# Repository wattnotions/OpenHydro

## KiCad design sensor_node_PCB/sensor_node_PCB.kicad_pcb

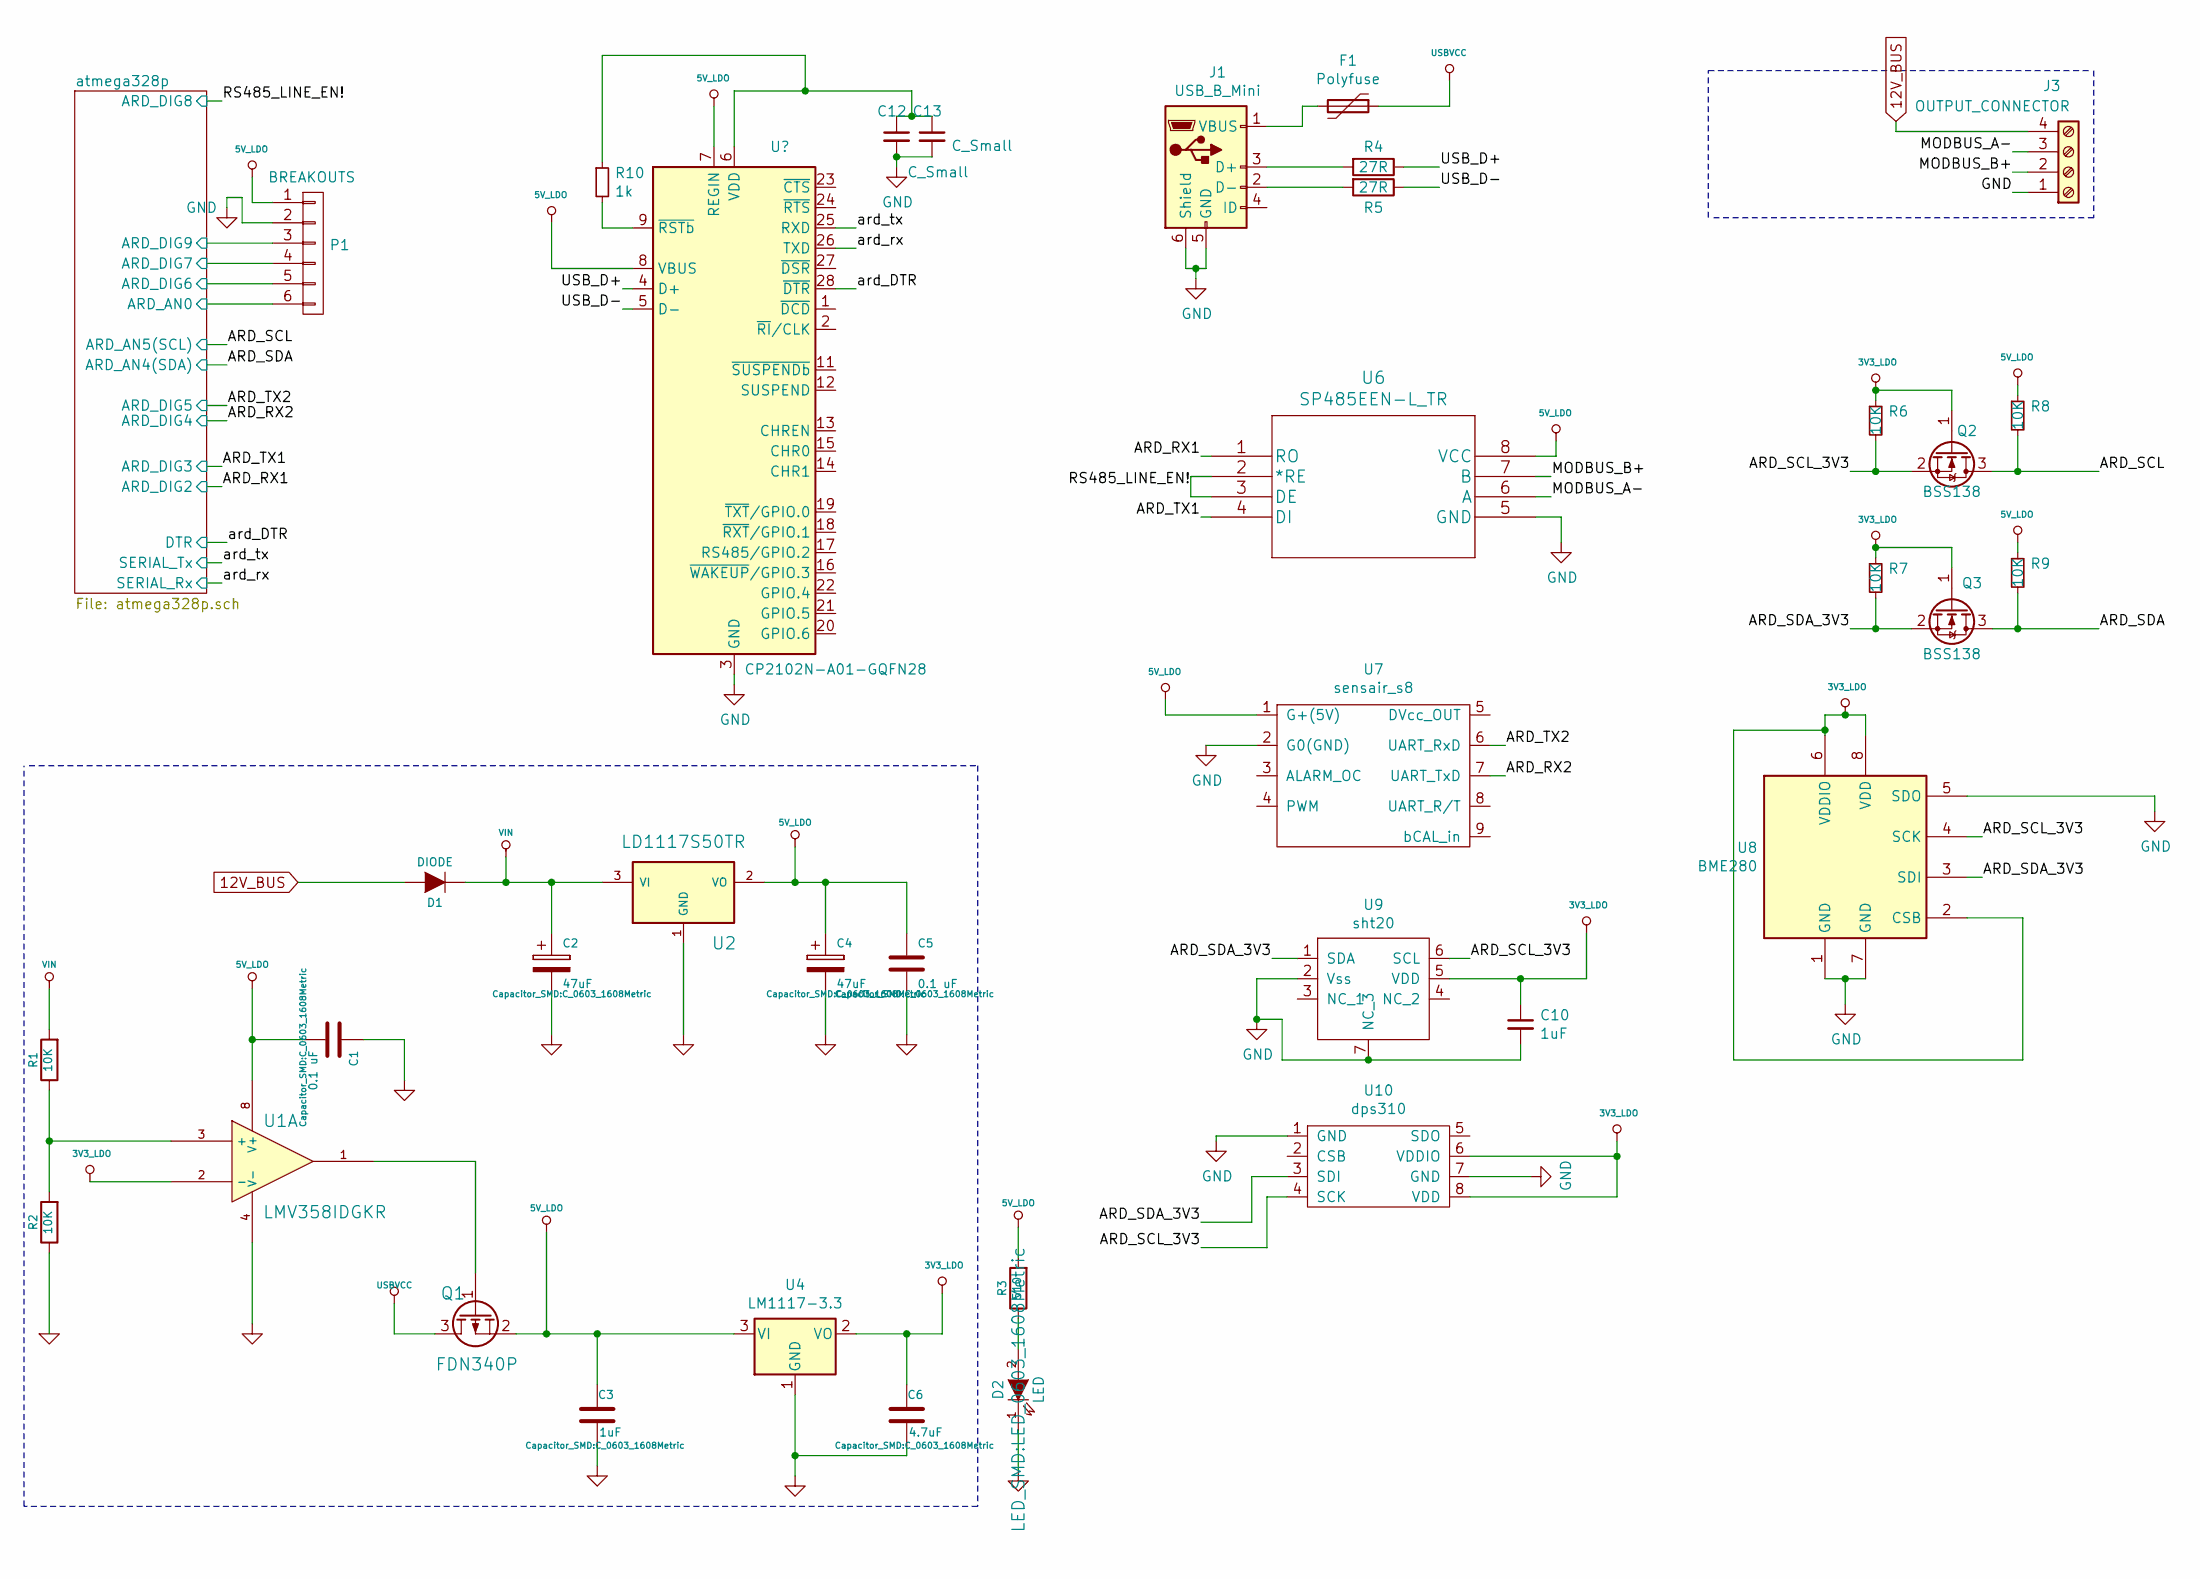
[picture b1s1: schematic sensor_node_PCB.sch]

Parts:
C1, C5: 0.1 uF; C_0603_1608Metric
C2, C4: 47uF; C_0603_1608Metric
C3, C10: 1uF; C_0603_1608Metric
C6: 4.7uF; C_0603_1608Metric
C12, C13: C_Small; C_0603_1608Metric
D1: DIODE; D_SOD-123
D2: LED; LED_0603_1608Metric
F1: Polyfuse; Fuse_1206_3216Metric
J1: USB_B_Mini; USB_Mini-B_Tensility_54-00023_Vertical
J3: OUTPUT_CONNECTOR; PhoenixContact_MSTB_2,5_4-GF-5,08_1x04_P5.08mm_Horizontal_T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
P1: BREAKOUTS; TerminalBlock_bornier-6_P5.08mm
Q1: FDN340P; SuperSOT-3
Q2, Q3: BSS138; SOT-23
R1, R2, R6, R7, R8, R9: 10K; R_0603_1608Metric
R3: 510; R_0603_1608Metric
R4, R5: 27R; R_0603_1608Metric
R10: 1k; R_0603_1608Metric
U1: LMV358IDGKR; SOIC-8_3.9x4.9mm_P1.27mm
U2: LD1117S50TR; SOT-223-3_TabPin2
U4: LM1117-3.3; SOT-223-3_TabPin2
U6: SP485EEN-L_TR; SOIC-8_3.9x4.9mm_P1.27mm
U7: sensair_s8; senseair_s8_v3
U8: BME280; Bosch_LGA-8_2.5x2.5mm_P0.65mm_ClockwisePinNumbering
U9: sht20; DFN-6-1EP_3x3mm_P1mm_EP1.5x2.4mm
U10: dps310; Bosch_LGA-8_2x2.5mm_P0.65mm_ClockwisePinNumbering

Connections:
3V3_LDO: C6.1, C10.1, Q2.1 (G), Q3.1 (G), R6.1, R7.1, U1.2 (-), U4.2 (VO), U8.2 (CSB), U8.6 (VDDIO), U8.8 (VDD), U9.5 (VDD), U10.6 (VDDIO), U10.8 (VDD)
5V_LDO: C1.2, C3.1, C4.1, C5.1, P1.1, Q1.2 (S), R3.2, R8.1, R9.1, U1.8 (V+), U2.2 (VO), U4.3 (VI), U6.8 (VCC), U7.1 (G+(5V)); also elsewhere on the board
12V_BUS: D1.2 (A), J3.4
/ARD_RX1: U6.1 (RO); also elsewhere on the board
/ARD_RX2: U7.7 (UART_TxD); also elsewhere on the board
/ARD_SCL: Q2.3 (D), R8.2; also elsewhere on the board
/ARD_SCL_3V3: Q2.2 (S), R6.2, U8.4 (SCK), U9.6 (SCL), U10.4 (SCK)
/ARD_SDA: Q3.3 (D), R9.2; also elsewhere on the board
/ARD_SDA_3V3: Q3.2 (S), R7.2, U8.3 (SDI), U9.1 (SDA), U10.3 (SDI)
/ARD_TX1: U6.4 (DI); also elsewhere on the board
/ARD_TX2: U7.6 (UART_RxD); also elsewhere on the board
/MODBUS_A-: J3.3, U6.6 (A)
/MODBUS_B+: J3.2, U6.7 (B)
/RS485_LINE_EN!: U6.2 (*RE), U6.3 (DE); also elsewhere on the board
/USB_D+: R4.1; also elsewhere on the board
/USB_D-: R5.1; also elsewhere on the board
/atmega328p/ARD_AN0: P1.6; also elsewhere on the board
/atmega328p/ARD_DIG6: P1.5; also elsewhere on the board
/atmega328p/ARD_DIG7: P1.4; also elsewhere on the board
/atmega328p/ARD_DIG9: P1.3; also elsewhere on the board
GND: C1.1, C2.2, C3.2, C4.2, C5.2, C6.2, C10.2, C12.2, C13.2, D2.1 (K), J1.5 (GND), J1.6 (Shield), J3.1, P1.2, R2.1, U1.4 (V-), U2.1 (GND), U4.1 (GND), U6.5 (GND), U7.2 (G0(GND)), U8.1 (GND), U8.5 (SDO), U8.7 (GND), U9.2 (Vss), U9.7 (NC_3), U10.1 (GND), U10.7 (GND); also elsewhere on the board
unnamed 32: C12.1, C13.1, R10.1; also elsewhere on the board
unnamed: D2.2 (A), R3.1
unnamed: F1.2, J1.1 (VBUS)
unnamed: J1.2 (D-), R5.2
unnamed: J1.3 (D+), R4.2
unnamed: Q1.1 (G), U1.1
unnamed: R1.1, R2.2, U1.3 (+)
unnamed 41: R10.2; also elsewhere on the board
USBVCC: F1.1, Q1.3 (D)
Vin: C2.1, D1.1 (K), R1.2, U2.3 (VI)

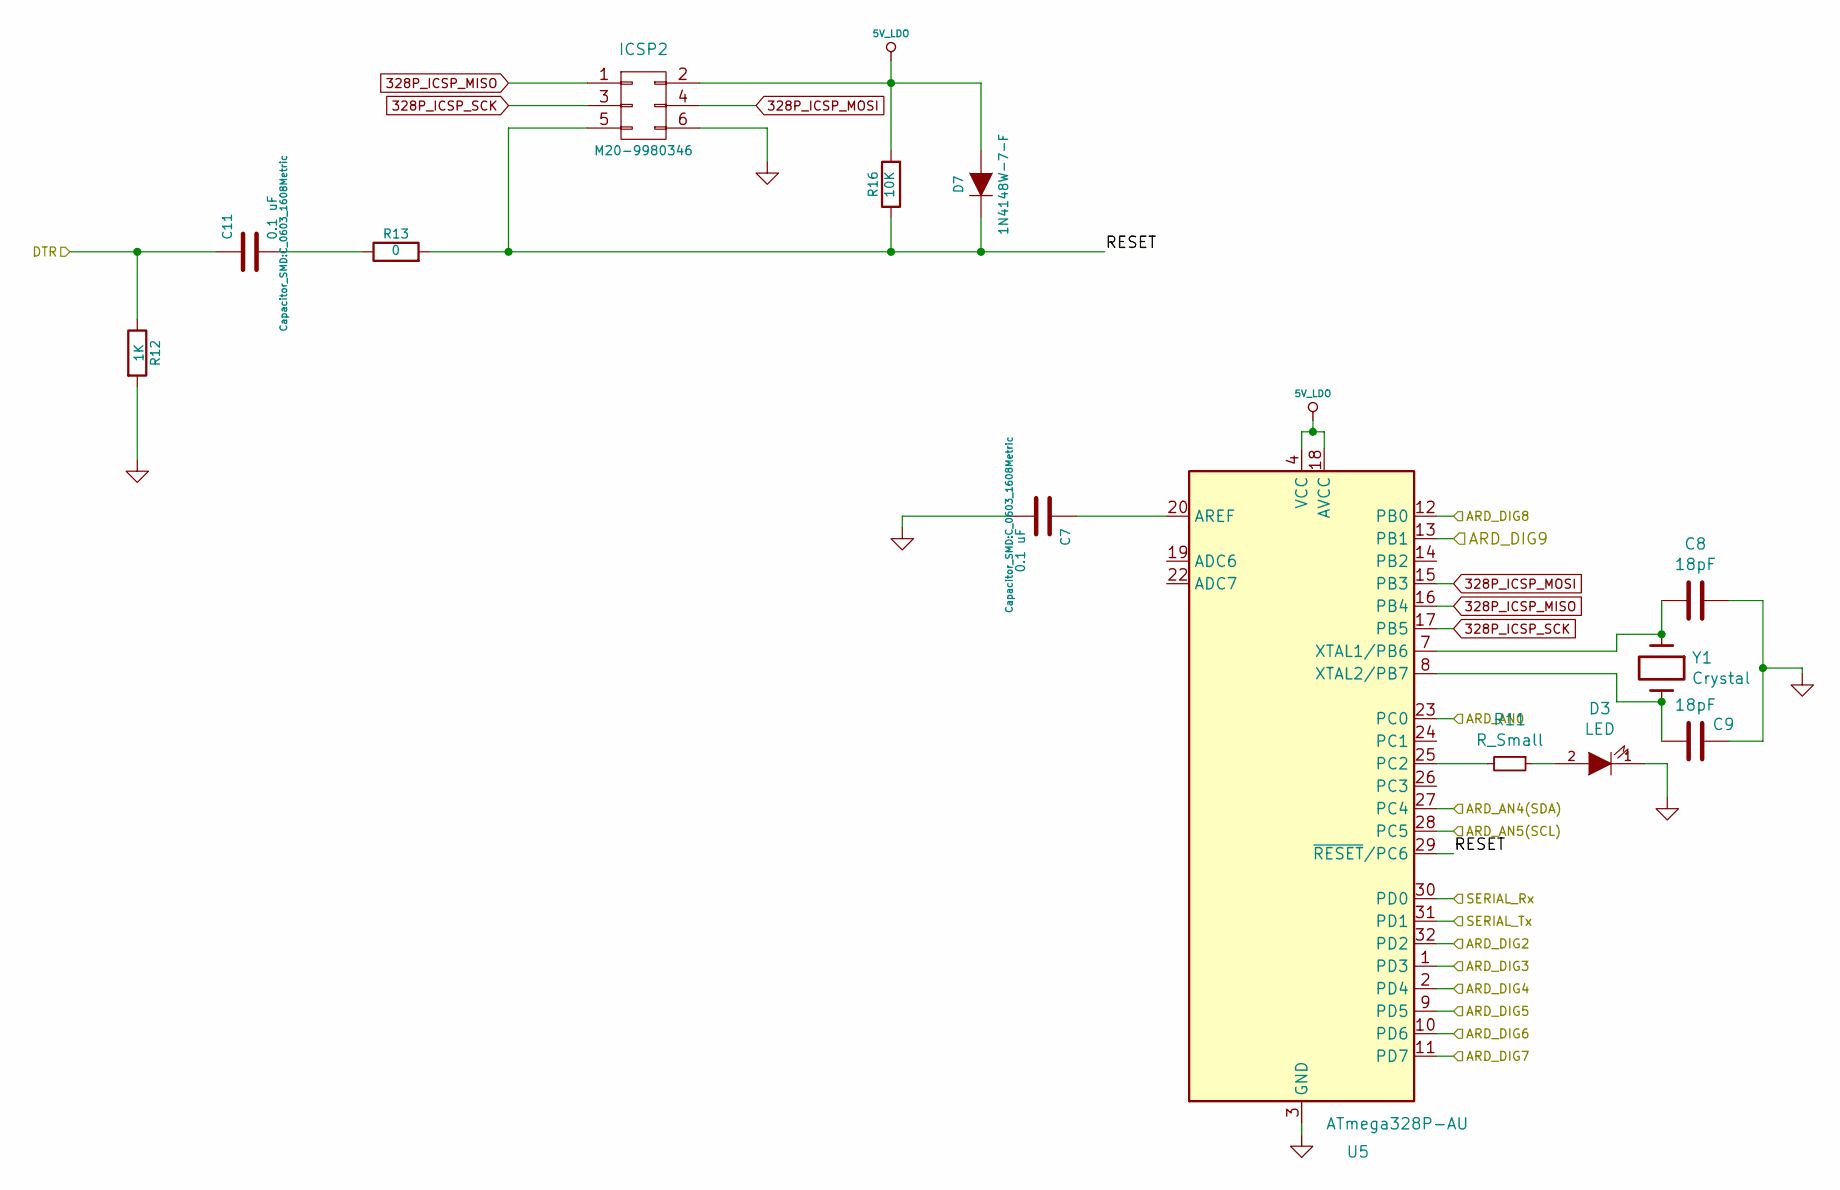
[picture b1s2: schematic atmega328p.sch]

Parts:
C7, C11: 0.1 uF; C_0603_1608Metric
C8, C9: 18pF; C_0603_1608Metric
D3: LED; LED_0603_1608Metric
D7: 1N4148W-7-F; D_SOD-123
ICSP2: M20-9980346; PinHeader_2x03_P2.54mm_Vertical_SMD
R11: R_Small; LED_0603_1608Metric
R12: 1K; R_0603_1608Metric
R13: 0; R_0603_1608Metric
R16: 10K; R_0603_1608Metric
U5: ATmega328P-AU; TQFP-32_7x7mm_P0.8mm
Y1: Crystal; Crystal_SMD_5032-2Pin_5.0x3.2mm

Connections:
5V_LDO: D7.2 (A), ICSP2.2, R16.2, U5.4 (VCC), U5.6 (VCC), U5.18 (AVCC); also elsewhere on the board
328P_ICSP_MISO: ICSP2.1, U5.16 (PB4)
328P_ICSP_MOSI: ICSP2.4, U5.15 (PB3)
328P_ICSP_SCK: ICSP2.3, U5.17 (PB5)
/ARD_RX1: U5.32 (PD2); also elsewhere on the board
/ARD_RX2: U5.2 (PD4); also elsewhere on the board
/ARD_SCL: U5.28 (PC5); also elsewhere on the board
/ARD_SDA: U5.27 (PC4); also elsewhere on the board
/ARD_TX1: U5.1 (PD3); also elsewhere on the board
/ARD_TX2: U5.9 (PD5); also elsewhere on the board
/RS485_LINE_EN!: U5.12 (PB0); also elsewhere on the board
/ard_DTR: C11.1, R12.1; also elsewhere on the board
/ard_rx: U5.30 (PD0); also elsewhere on the board
/ard_tx: U5.31 (PD1); also elsewhere on the board
/atmega328p/ARD_AN0: U5.23 (PC0); also elsewhere on the board
/atmega328p/ARD_DIG6: U5.10 (PD6); also elsewhere on the board
/atmega328p/ARD_DIG7: U5.11 (PD7); also elsewhere on the board
/atmega328p/ARD_DIG9: U5.13 (PB1); also elsewhere on the board
/atmega328p/RESET: D7.1 (K), ICSP2.5, R13.2, R16.1, U5.29 (~RESET~/PC6)
GND: C7.2, C8.1, C9.1, D3.1 (K), ICSP2.6, R12.2, U5.3 (GND), U5.5 (GND), U5.21 (GND); also elsewhere on the board
unnamed: C7.1, U5.20 (AREF)
unnamed: C8.2, U5.7 (XTAL1/PB6), Y1.1
unnamed: C9.2, U5.8 (XTAL2/PB7), Y1.2
unnamed: C11.2, R13.1
unnamed: D3.2 (A), R11.1
unnamed: R11.2, U5.25 (PC2)

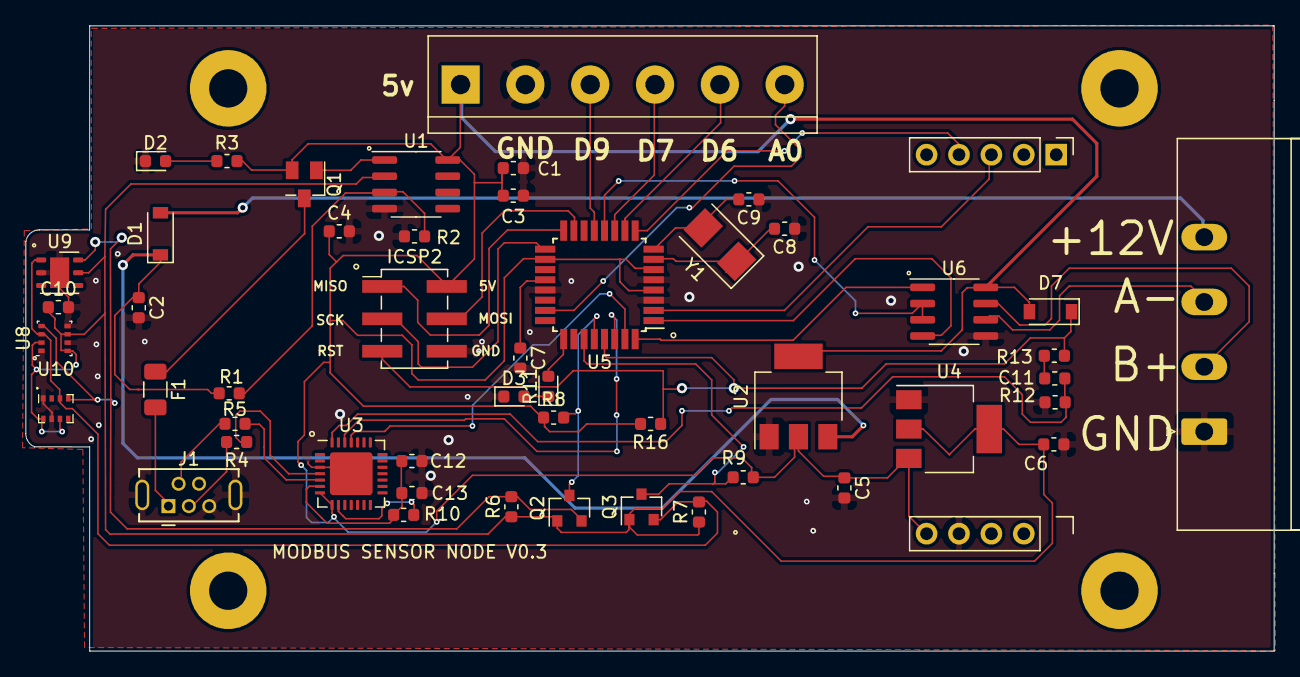
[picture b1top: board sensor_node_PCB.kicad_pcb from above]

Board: 2 copper layers, 97.8 x 49.0 mm, 50 parts (0 on the bottom side), 44 nets.

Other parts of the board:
U3: CP2102N-A01-GQFN28; QFN-28-1EP_5x5mm_P0.5mm_EP3.35x3.35mm

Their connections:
5V_LDO: U3.7, U3.8; also elsewhere on the board
/USB_D+: U3.4; also elsewhere on the board
/USB_D-: U3.5; also elsewhere on the board
/ard_DTR: U3.28; also elsewhere on the board
/ard_rx: U3.26; also elsewhere on the board
/ard_tx: U3.25; also elsewhere on the board
GND: U3.3, U3.29; also elsewhere on the board
unnamed 32: U3.6; also elsewhere on the board
unnamed 41: U3.9; also elsewhere on the board

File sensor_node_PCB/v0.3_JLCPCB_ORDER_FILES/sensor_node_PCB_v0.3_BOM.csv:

Comment,Designator,Footprint,LCSC
"C_Small","C12,C13","Capacitor_SMD:C_0603_1608Metric",""
"47uF","C2,C4","Capacitor_SMD:C_0603_1608Metric",""
"1uF","C3,C10","Capacitor_SMD:C_0603_1608Metric",""
"0.1 uF","C1,C5,C7,C11","Capacitor_SMD:C_0603_1608Metric",""
"4.7uF","C6","Capacitor_SMD:C_0603_1608Metric",""
"18pF","C8,C9","Capacitor_SMD:C_0603_1608Metric",""
"DIODE","D1","Diode_SMD:D_SOD-123",""
"LED","D2,D3","LED_SMD:LED_0603_1608Metric",""
"1N4148W-7-F","D7","Diode_SMD:D_SOD-123",""
"Polyfuse","F1","Fuse:Fuse_1206_3216Metric",""
"M20-9980346","ICSP2","Connector_PinHeader_2.54mm:PinHeader_2x03_P2.54mm_Vertical_SMD",""
"USB_B_Mini","J1","Connector_USB:USB_Mini-B_Tensility_54-00023_Vertical",""
"OUTPUT_CONNECTOR","J3","Connector_Phoenix_MSTB:PhoenixContact_MSTB_2,5_4-GF-5,08_1x04_P5.08mm_Horizontal_ThreadedFlange",""
"BREAKOUTS","P1","TerminalBlock:TerminalBlock_bornier-6_P5.08mm",""
"FDN340P","Q1","Package_TO_SOT_SMD:SuperSOT-3",""
"BSS138","Q2,Q3","Package_TO_SOT_SMD:SOT-23",""
"1k","R10","Resistor_SMD:R_0603_1608Metric",""
"R_Small","R11","LED_SMD:LED_0603_1608Metric",""
"1K","R12","Resistor_SMD:R_0603_1608Metric",""
"0","R13","Resistor_SMD:R_0603_1608Metric",""
"510","R3","Resistor_SMD:R_0603_1608Metric",""
"27R","R4,R5","Resistor_SMD:R_0603_1608Metric",""
"10K","R1,R2,R6,R7,R8,R9,R16","Resistor_SMD:R_0603_1608Metric",""
"LMV358IDGKR","U1","Package_SO:SOIC-8_3.9x4.9mm_P1.27mm",""
"dps310","U10","Package_LGA:Bosch_LGA-8_2x2.5mm_P0.65mm_ClockwisePinNumbering",""
"LD1117S50TR","U2","Package_TO_SOT_SMD:SOT-223-3_TabPin2",""
"CP2102N-A01-GQFN28","U3","Package_DFN_QFN:QFN-28-1EP_5x5mm_P0.5mm_EP3.35x3.35mm",""
"LM1117-3.3","U4","Package_TO_SOT_SMD:SOT-223-3_TabPin2",""
"ATmega328P-AU","U5","Package_QFP:TQFP-32_7x7mm_P0.8mm",""
"SP485EEN-L_TR","U6","Package_SO:SOIC-8_3.9x4.9mm_P1.27mm",""
"sensair_s8","U7","kicad_footprints:senseair_s8_v3",""
"BME280","U8","Package_LGA:Bosch_LGA-8_2.5x2.5mm_P0.65mm_ClockwisePinNumbering",""
"sht20","U9","Package_DFN_QFN:DFN-6-1EP_3x3mm_P1mm_EP1.5x2.4mm",""
"Crystal","Y1","Crystal:Crystal_SMD_5032-2Pin_5.0x3.2mm",""

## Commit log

2020-08-29 Changed folder structure
2020-08-30 mqtt dht11 test example working
2020-08-30 created kicad project
2020-08-30 changed ip to domain
2020-08-30 almost working - publish response needed
2020-09-01 added arduino uno schematic
2020-09-01 removed 3.3v reg and changed to 4 pin conn input
2020-09-01 added usb circuitry
2020-09-01 added modbus connectors
2020-09-01 changed 12v input to global label
2020-09-01 added 3.3v regulator
2020-09-02 changed rs485 transceiver to sp485e
2020-09-02 changed dir structure
2020-09-02 added datasheet
2020-09-02 started bme280 wiring
2020-09-03 added sensair s8
2020-09-03 added level shift app note
2020-09-03 added level shifter for bme280
2020-09-03 changed bme280 to use i2c
2020-09-03 ADDED BREAKOUT PINS
2020-09-04 schematic finished
2020-09-04 assign footprints 80% completed
2020-09-05 routing started 15%
2020-09-06 routing 50%
2020-09-06 routing 60% completed
2020-09-06 started placing mounting holes
2020-09-06 edge cuts layer with mounting holes complete
2020-09-06 routing complete
2020-09-07 made 12v bus line bigger and moved away from bme280
2020-09-07 added missing dtr trace
2020-09-07 moved vin trace away from bme280
2020-09-07 fixed senseair s8 pin mixup - added lots of silk text
2020-09-08 changed board outline to rectangle
2020-09-14 working publish example
2020-09-14 added json print just to see formatting
2020-09-20 rpc receive almost fully working
2020-09-21 progressed rpc response, not quite there
2020-09-21 fixed incorrect atmega328p pinout
2020-09-21 cleaned up drc violations
2020-09-21 removed 2nd connector - fixed mounting holes
2020-09-23 generated files for jlcpcb fab
2020-09-23 rpc mqtt receive and ack working
2020-10-03 bme280 comms working
2020-10-03 added senseair s8 library
2020-10-03 working s8 example
2020-10-03 silkscreen cleanup
2020-10-03 added s8 modbus/uart datasheet
2020-10-17 working softserial modbus example
2020-10-17 modbus read mqtt send basic example working!!
    need to look at main loop, not written correctly from mqtt pov need client.loop() in there somewhere
2020-10-17 added bme280 code with modbus code....working
2020-10-24 got temp float formatting working
2020-10-24 temp, humidity and pressure mqtt send working
2020-10-24 fixed main loop - more mqtt keepalive friendly
2020-10-24 dir rename
2020-10-24 dashboard save addded
2020-10-24 added comments
2020-10-25 added c02 code and extra comments
2020-10-25 c02 modbus read working
2020-10-25 co2 modbus read from slave working
2020-10-25 started design spec document
2020-11-01 added img upload scripts
2020-11-01 updated design spec
2020-11-03 added crontab with thingboard service restart
2020-11-07 more descriptive file name
2020-12-12 made eagle project
2020-12-12 added ltspice files
2020-12-12 dir restructure
2020-12-12 added sensor node case 3d print files
2020-12-12 added analog circuitry
2020-12-12 made .brd file
2020-12-13 part placement completed
2020-12-19 made centroid file
2020-12-19 added external tab for bme280 ic
2020-12-19 moved bme280 to tab
2020-12-19 added tab to gnd fill zone
2020-12-19 put curved edges on tab
2020-12-19 replaced missing gnd plane
2020-12-19 fixed max485 wiring issues on schematic
2020-12-19 routed max485 en to ard d8
2020-12-19 added sht20 to tab
2020-12-20 added dps310 to schem and board
2020-12-20 changed term block to 5.08mm - added silk pin labels
2020-12-20 changed usb ic to cp2102 on schematic
2020-12-20 cp2102 routing complete
2020-12-20 added status led to pin 25
2020-12-20 made term block silk invisible
2020-12-20 changed cp2102 to 28 pin version
2020-12-20 generated fab files
2020-12-30 changed screw terminals to correct size
2020-12-30 kicad files
2020-12-30 added silk screen text
2020-12-30 added 1.5k pull down resistor to all inputs
2020-12-30 added board name + version to silk text
2020-12-30 made board a bit bigger
2020-12-30 fixed silk text wrong layer
2020-12-30 fixed another silk issue- generated gerbers for v0.2
2020-12-30 changed pulldown resistors to 1.5k instead of 10k
2021-03-06 got JSON parse working
2021-03-06 made json parse add on func
2021-03-06 fixed bug with SP update func
2021-03-06 fixed typo
2021-03-08 fixed bug with temp SP knob update
2021-04-11 works but have slave select bug occurs
2021-05-03 reverted to a previous working commit
2021-05-03 changed slave address to 5
2021-05-03 added slave address print from mem addr 5
2021-05-03 address printing from slaves is working
    can now tell the two slaves apart
2021-05-03 added save sensor values in local variables
2021-05-03 basic on off control implemented - untested
